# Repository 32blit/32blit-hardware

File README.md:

# 32Blit Hardware

This repository includes the schematic and STM32 Cube files for the 32Blit console.

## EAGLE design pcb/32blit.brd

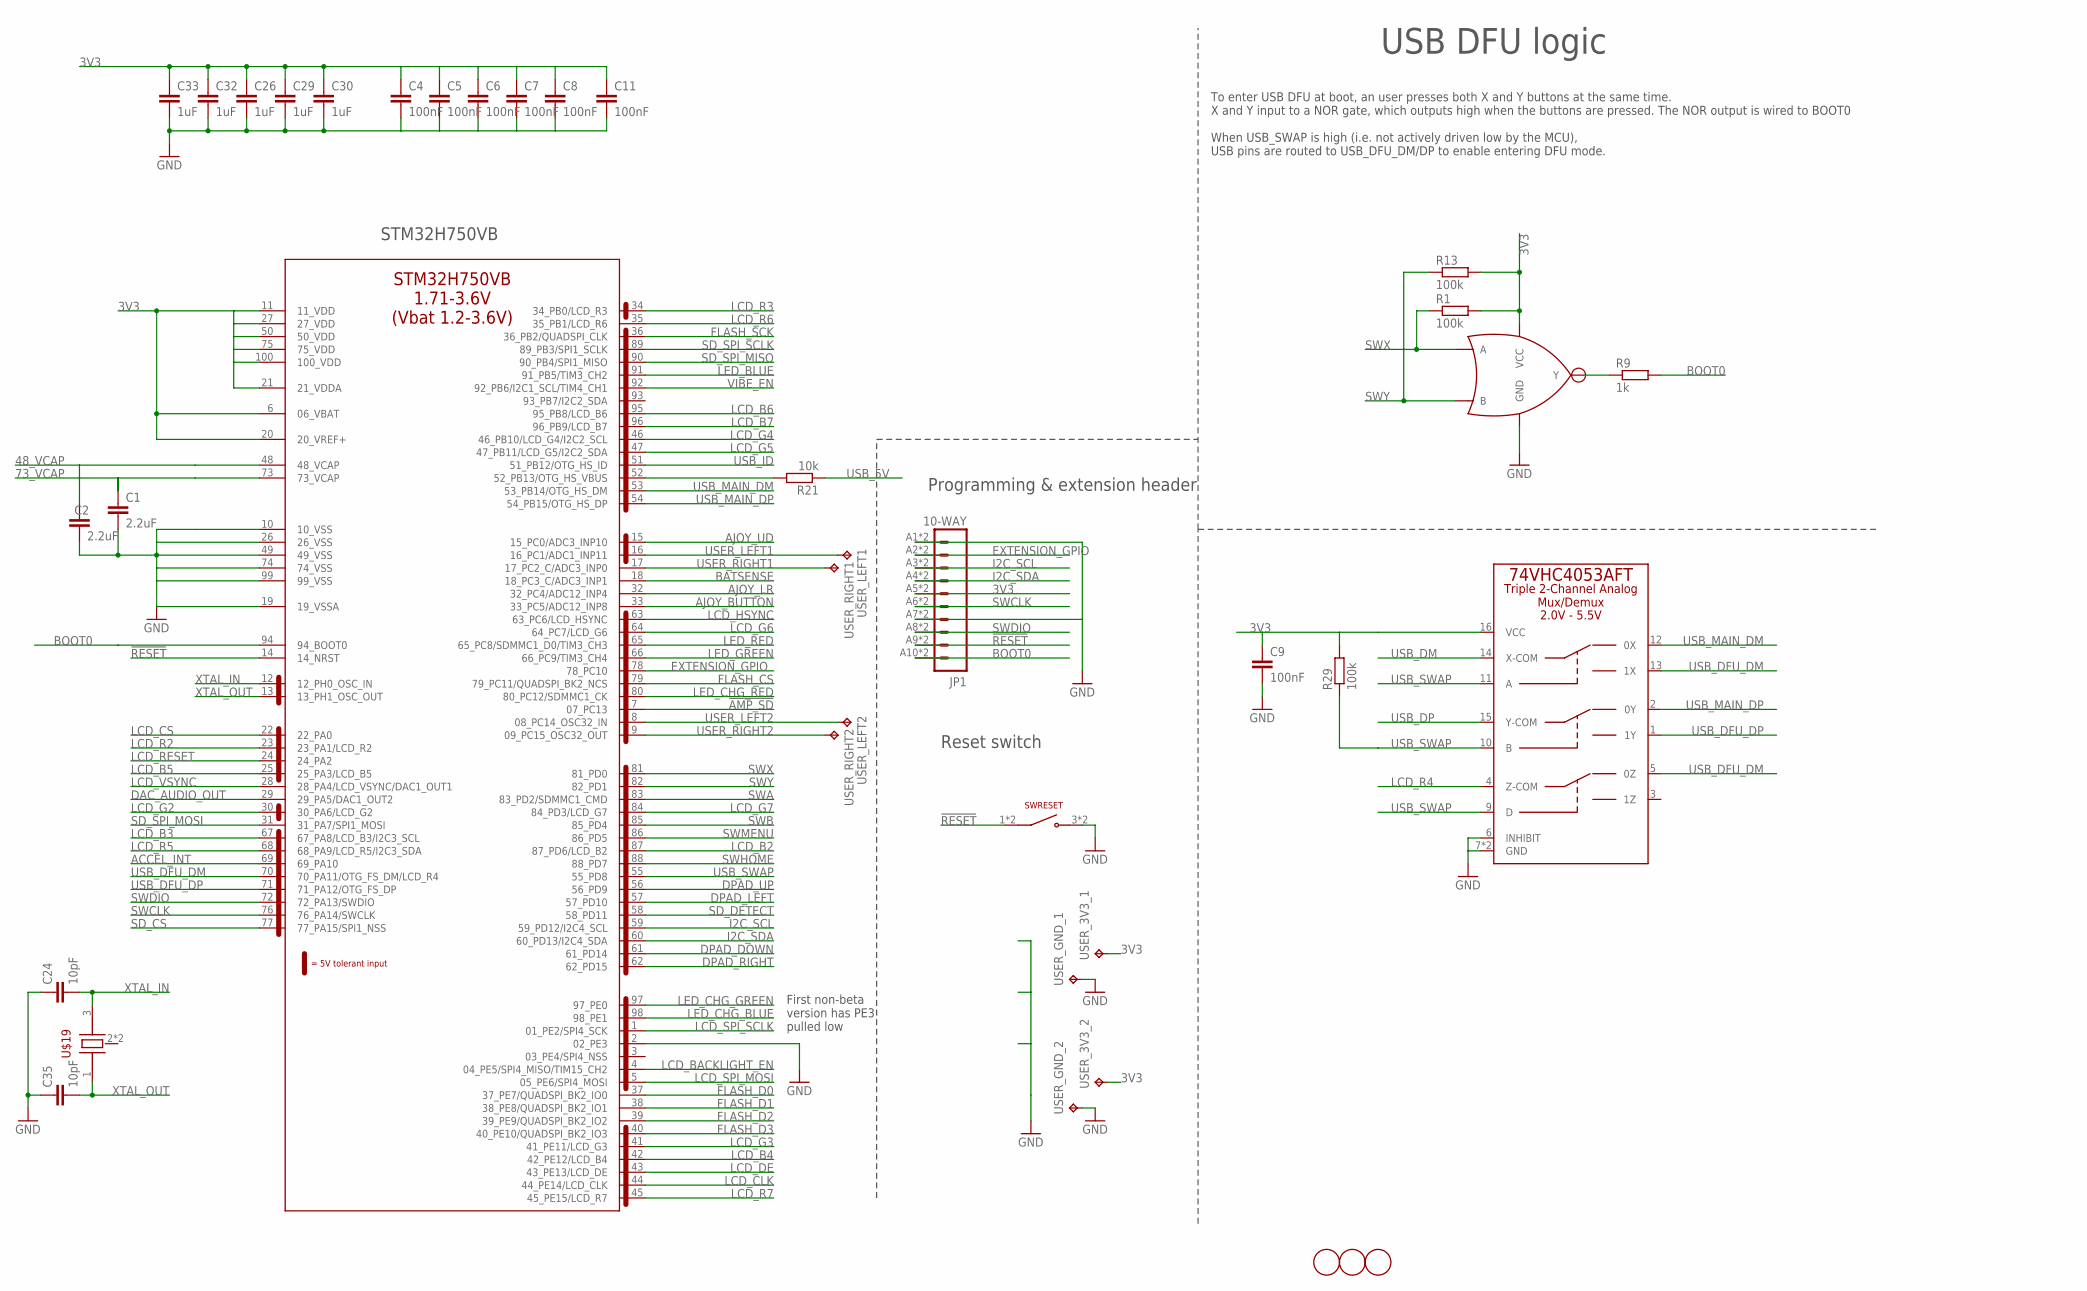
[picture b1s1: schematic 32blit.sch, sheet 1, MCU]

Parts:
C1, C2: 2.2uF; C0603
C4, C5, C6, C7, C8, C9, C11: 100nF; C0402K
C24, C35: 10pF; C0603K
C26, C29, C30, C32, C33: 1uF; C0603
JP1: 10-WAY; 1X10_FEMALE_SMT_RIGHT_ANGLE
R1, R13, R29: 100k; R0603
R9: 1k; R0603
R21: 10k; R0603
STM32H750: STM32H750VB; LQFP-100
SWRESET: LY-A03-02; TACT_RIGHT_ANGLE_LOW_PROFILE
U1: SN74AHC1G02; SOT-23-5
U8: 74VHC4053AFT; TSSOP-16-TI
U$17, U$22, U$23: FIDUCIAL1MM; FIDUCIAL-1MM
U$19: ABM8G-12.000MHZ-4Y-T3; TSX-3225
USER_3V3_1, USER_3V3_2: TPTP17SQ; TP17SQ
USER_GND_1, USER_GND_2: TPTP17SQ; TP17SQ
USER_LEFT1, USER_LEFT2: TPTP17SQ; TP17SQ
USER_RIGHT1, USER_RIGHT2: TPTP17SQ; TP17SQ

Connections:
3V3: C4.1, C5.1, C6.1, C7.1, C8.1, C9.1, C11.1, C26.1, C29.1, C30.1, C32.1, C33.1, JP1.A5 (5), JP1.B5 (5), R1.2, R13.2, R29.2, STM32H750.6 (06_VBAT), STM32H750.11 (11_VDD), STM32H750.20 (20_VREF+), STM32H750.21 (21_VDDA), STM32H750.27 (27_VDD), STM32H750.50 (50_VDD), STM32H750.75 (75_VDD), STM32H750.100 (100_VDD), U1.5 (VCC), U8.16 (VCC), USER_3V3_1.TP, USER_3V3_2.TP; also elsewhere on the board
48_VCAP: C2.1, STM32H750.48 (48_VCAP)
73_VCAP: C1.1, STM32H750.73 (73_VCAP)
!AMP_SD: STM32H750.7 (07_PC13); also elsewhere on the board
!RESET: JP1.A9 (9), JP1.B9 (9), STM32H750.14 (14_NRST), SWRESET.1, SWRESET.2 (1)
ACCEL_INT: STM32H750.69 (69_PA10); also elsewhere on the board
AJOY_BUTTON: STM32H750.33 (33_PC5/ADC12_INP8); also elsewhere on the board
AJOY_LR: STM32H750.32 (32_PC4/ADC12_INP4); also elsewhere on the board
AJOY_UD: STM32H750.15 (15_PC0/ADC3_INP10); also elsewhere on the board
BATSENSE: STM32H750.18 (18_PC3_C/ADC3_INP1); also elsewhere on the board
BOOT0: JP1.A10 (10), JP1.B10 (10), R9.2, STM32H750.94 (94_BOOT0)
DAC_AUDIO_OUT: STM32H750.29 (29_PA5/DAC1_OUT2); also elsewhere on the board
DPAD_DOWN: STM32H750.61 (61_PD14); also elsewhere on the board
DPAD_LEFT: STM32H750.57 (57_PD10); also elsewhere on the board
DPAD_RIGHT: STM32H750.62 (62_PD15); also elsewhere on the board
DPAD_UP: STM32H750.56 (56_PD9); also elsewhere on the board
EXTENSION_GPIO: JP1.A2 (2), JP1.B2 (2), STM32H750.78 (78_PC10)
FLASH_CS: STM32H750.79 (79_PC11/QUADSPI_BK2_NCS); also elsewhere on the board
FLASH_D0: STM32H750.37 (37_PE7/QUADSPI_BK2_IO0); also elsewhere on the board
FLASH_D1: STM32H750.38 (38_PE8/QUADSPI_BK2_IO1); also elsewhere on the board
FLASH_D2: STM32H750.39 (39_PE9/QUADSPI_BK2_IO2); also elsewhere on the board
FLASH_D3: STM32H750.40 (40_PE10/QUADSPI_BK2_IO3); also elsewhere on the board
FLASH_SCK: STM32H750.36 (36_PB2/QUADSPI_CLK); also elsewhere on the board
GND: C1.2, C2.2, C4.2, C5.2, C6.2, C7.2, C8.2, C9.2, C11.2, C24.1, C26.2, C29.2, C30.2, C32.2, C33.2, C35.1, JP1.A1 (1), JP1.A7 (7), JP1.B1 (1), JP1.B7 (7), STM32H750.2 (02_PE3), STM32H750.10 (10_VSS), STM32H750.19 (19_VSSA), STM32H750.26 (26_VSS), STM32H750.49 (49_VSS), STM32H750.74 (74_VSS), STM32H750.99 (99_VSS), SWRESET.3 (2), SWRESET.4 (2), U1.3 (GND), U8.6 (INHIBIT), U8.7 (GND), U8.8 (GND), USER_GND_1.TP, USER_GND_2.TP; also elsewhere on the board
I2C_SCL: JP1.A3 (3), JP1.B3 (3), STM32H750.59 (59_PD12/I2C4_SCL); also elsewhere on the board
I2C_SDA: JP1.A4 (4), JP1.B4 (4), STM32H750.60 (60_PD13/I2C4_SDA); also elsewhere on the board
LCD_B2: STM32H750.87 (87_PD6/LCD_B2); also elsewhere on the board
LCD_B3: STM32H750.67 (67_PA8/LCD_B3/I2C3_SCL); also elsewhere on the board
LCD_B4: STM32H750.42 (42_PE12/LCD_B4); also elsewhere on the board
LCD_B5: STM32H750.25 (25_PA3/LCD_B5); also elsewhere on the board
LCD_B6: STM32H750.95 (95_PB8/LCD_B6); also elsewhere on the board
LCD_B7: STM32H750.96 (96_PB9/LCD_B7); also elsewhere on the board
LCD_BACKLIGHT_EN: STM32H750.4 (04_PE5/SPI4_MISO/TIM15_CH2); also elsewhere on the board
LCD_CLK: STM32H750.44 (44_PE14/LCD_CLK); also elsewhere on the board
LCD_CS: STM32H750.22 (22_PA0); also elsewhere on the board
LCD_DE: STM32H750.43 (43_PE13/LCD_DE); also elsewhere on the board
LCD_G2: STM32H750.30 (30_PA6/LCD_G2); also elsewhere on the board
LCD_G3: STM32H750.41 (41_PE11/LCD_G3); also elsewhere on the board
LCD_G4: STM32H750.46 (46_PB10/LCD_G4/I2C2_SCL); also elsewhere on the board
LCD_G5: STM32H750.47 (47_PB11/LCD_G5/I2C2_SDA); also elsewhere on the board
LCD_G6: STM32H750.64 (64_PC7/LCD_G6); also elsewhere on the board
LCD_G7: STM32H750.84 (84_PD3/LCD_G7); also elsewhere on the board
LCD_HSYNC: STM32H750.63 (63_PC6/LCD_HSYNC); also elsewhere on the board
LCD_R2: STM32H750.23 (23_PA1/LCD_R2); also elsewhere on the board
LCD_R3: STM32H750.34 (34_PB0/LCD_R3); also elsewhere on the board
LCD_R4: U8.4 (Z-COM); also elsewhere on the board
LCD_R5: STM32H750.68 (68_PA9/LCD_R5/I2C3_SDA); also elsewhere on the board
LCD_R6: STM32H750.35 (35_PB1/LCD_R6); also elsewhere on the board
LCD_R7: STM32H750.45 (45_PE15/LCD_R7); also elsewhere on the board
LCD_RESET: STM32H750.24 (24_PA2); also elsewhere on the board
LCD_SPI_MOSI: STM32H750.5 (05_PE6/SPI4_MOSI); also elsewhere on the board
LCD_SPI_SCLK: STM32H750.1 (01_PE2/SPI4_SCK); also elsewhere on the board
LCD_VSYNC: STM32H750.28 (28_PA4/LCD_VSYNC/DAC1_OUT1); also elsewhere on the board
LED_BLUE: STM32H750.91 (91_PB5/TIM3_CH2); also elsewhere on the board
LED_CHG_BLUE: STM32H750.98 (98_PE1); also elsewhere on the board
LED_CHG_GREEN: STM32H750.97 (97_PE0); also elsewhere on the board
LED_CHG_RED: STM32H750.80 (80_PC12/SDMMC1_CK); also elsewhere on the board
LED_GREEN: STM32H750.66 (66_PC9/TIM3_CH4); also elsewhere on the board
LED_RED: STM32H750.65 (65_PC8/SDMMC1_D0/TIM3_CH3); also elsewhere on the board
unnamed: R9.1, U1.4 (Y)
unnamed: R21.2, STM32H750.52 (52_PB13/OTG_HS_VBUS)
SD_CS: STM32H750.77 (77_PA15/SPI1_NSS); also elsewhere on the board
SD_DETECT: STM32H750.58 (58_PD11); also elsewhere on the board
SD_SPI_MISO: STM32H750.90 (90_PB4/SPI1_MISO); also elsewhere on the board
SD_SPI_MOSI: STM32H750.31 (31_PA7/SPI1_MOSI); also elsewhere on the board
SD_SPI_SCLK: STM32H750.89 (89_PB3/SPI1_SCLK); also elsewhere on the board
SWA: STM32H750.83 (83_PD2/SDMMC1_CMD); also elsewhere on the board
SWB: STM32H750.85 (85_PD4); also elsewhere on the board
SWCLK: JP1.A6 (6), JP1.B6 (6), STM32H750.76 (76_PA14/SWCLK)
SWDIO: JP1.A8 (8), JP1.B8 (8), STM32H750.72 (72_PA13/SWDIO)
SWHOME: STM32H750.88 (88_PD7); also elsewhere on the board
SWMENU: STM32H750.86 (86_PD5); also elsewhere on the board
SWX: R1.1, STM32H750.81 (81_PD0), U1.1 (A); also elsewhere on the board
SWY: R13.1, STM32H750.82 (82_PD1), U1.2 (B); also elsewhere on the board
USB_5V: R21.1; also elsewhere on the board
USB_DFU_DM: STM32H750.70 (70_PA11/OTG_FS_DM/LCD_R4), U8.5 (0Z), U8.13 (1X)
USB_DFU_DP: STM32H750.71 (71_PA12/OTG_FS_DP), U8.1 (1Y)
USB_DM: U8.14 (X-COM); also elsewhere on the board
USB_DP: U8.15 (Y-COM); also elsewhere on the board
USB_ID: STM32H750.51 (51_PB12/OTG_HS_ID); also elsewhere on the board
USB_MAIN_DM: STM32H750.53 (53_PB14/OTG_HS_DM), U8.12 (0X)
USB_MAIN_DP: STM32H750.54 (54_PB15/OTG_HS_DP), U8.2 (0Y)
USB_SWAP: R29.1, STM32H750.55 (55_PD8), U8.9 (D), U8.10 (B), U8.11 (A)
USER_LEFT1: STM32H750.16 (16_PC1/ADC1_INP11), USER_LEFT1.TP
USER_LEFT2: STM32H750.8 (08_PC14_OSC32_IN), USER_LEFT2.TP
USER_RIGHT1: STM32H750.17 (17_PC2_C/ADC3_INP0), USER_RIGHT1.TP
USER_RIGHT2: STM32H750.9 (09_PC15_OSC32_OUT), USER_RIGHT2.TP
VIBE_EN: STM32H750.92 (92_PB6/I2C1_SCL/TIM4_CH1); also elsewhere on the board
XTAL_IN: C24.2, STM32H750.12 (12_PH0_OSC_IN), U$19.3 (2)
XTAL_OUT: C35.2, STM32H750.13 (13_PH1_OSC_OUT), U$19.1

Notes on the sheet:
STM32H750VB
Programming & extension header
Reset switch
To enter USB DFU at boot, an user presses both X and Y buttons at the same time. X and Y input to a NOR gate, which outputs high when the buttons are pressed. The NOR output is wired to BOOT0 When USB_SWAP is high (i.e. not actively driven low by the MCU), USB pins are routed to USB_DFU_DM/DP to en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
USB DFU logic
First non-beta version has PE3 pulled low

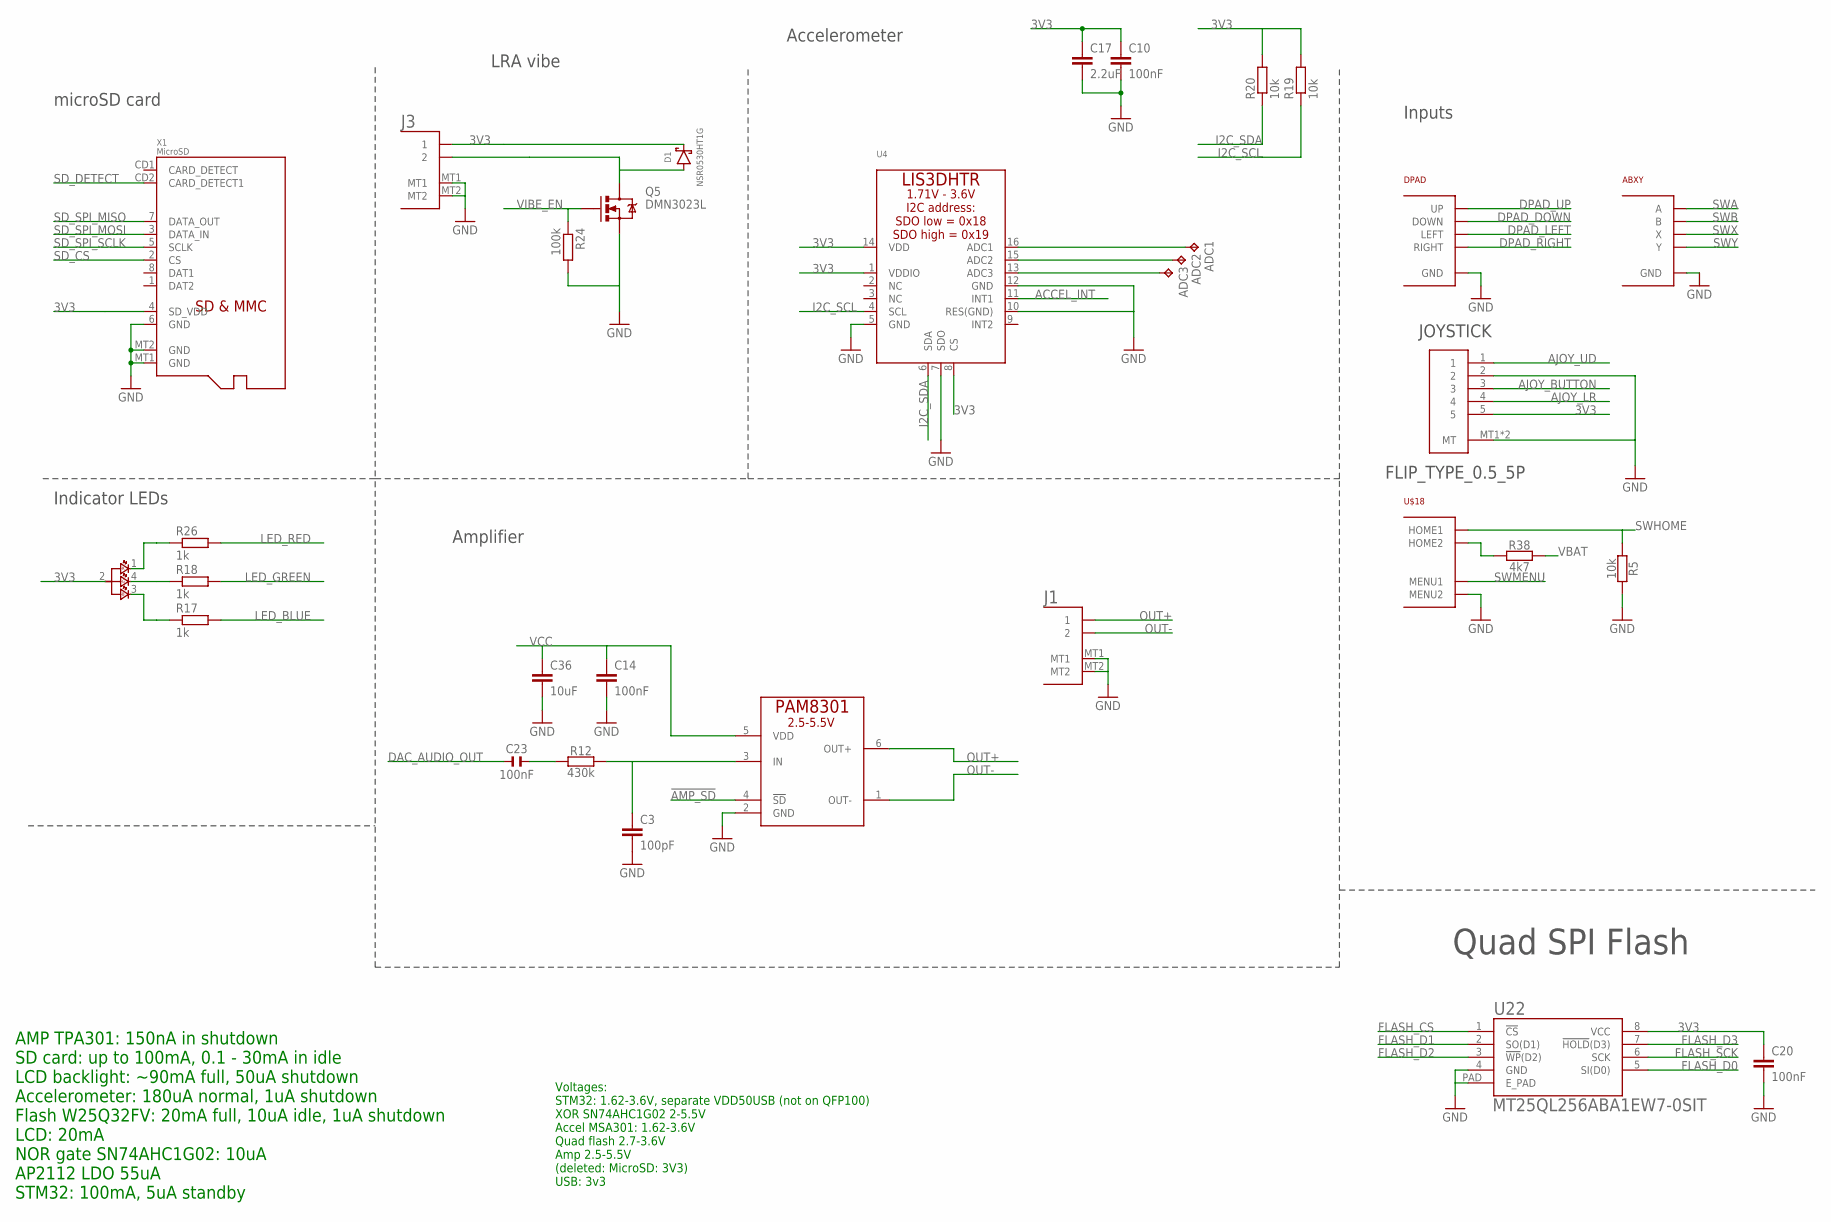
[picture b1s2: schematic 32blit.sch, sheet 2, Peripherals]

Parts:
ABXY: ABXY
ADC1, ADC2, ADC3: TPTP17SQ; TP17SQ
C3: 100pF; C0603
C10, C14, C20: 100nF; C0402K
C17: 2.2uF; C0603
C23: 100nF; 0402
C36: 10uF; C0805
D1: NSR0530HT1G; SOD-323
DPAD: DPAD
J1: 1X02PICOBLADE; PICOBLADE_1.25MM_2P
J3: 1X02JST_SH; JST_SH_1.0MM_2P
JOYSTICK: FLIP_TYPE_0.5_5P; FPC-0.5MM-05WAY
Q5: DMN3023L; SOT23
R5, R19, R20: 10k; R0603
R12: 430k; R0603
R17, R18, R26: 1k; R0603
R24: 100k; R0603
R38: 4k7; R0603
RGB2: LED_RGB_4P6028_REVERSE; LED-6028_REVERSE_RGB
U4: ACCEL_LIS3DHTR; LGA16_3X3MM
U5: PAM8301; SOT-23-6
U22: MT25QL256ABA1EW7-0SIT; DFN-8_6X5MM
U$18: HOME-MENU; MENU-HOME
X1: MicroSD; MICROSD

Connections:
3V3: C10.1, C17.1, C20.1, D1.C, J3.1, JOYSTICK.5, R19.2, R20.2, RGB2.2 (A), U4.1 (VDDIO), U4.8 (CS), U4.14 (VDD), U22.8 (VCC), X1.4 (SD_VDD); also elsewhere on the board
!AMP_SD: U5.4 (!SD); also elsewhere on the board
ACCEL_INT: U4.11 (INT1); also elsewhere on the board
AJOY_BUTTON: JOYSTICK.3; also elsewhere on the board
AJOY_LR: JOYSTICK.4; also elsewhere on the board
AJOY_UD: JOYSTICK.1; also elsewhere on the board
DAC_AUDIO_OUT: C23.2; also elsewhere on the board
DPAD_DOWN: DPAD.DOWN; also elsewhere on the board
DPAD_LEFT: DPAD.LEFT; also elsewhere on the board
DPAD_RIGHT: DPAD.RIGHT; also elsewhere on the board
DPAD_UP: DPAD.UP; also elsewhere on the board
FLASH_CS: U22.1 (!CS); also elsewhere on the board
FLASH_D0: U22.5 (SI(D0)); also elsewhere on the board
FLASH_D1: U22.2 (SO(D1)); also elsewhere on the board
FLASH_D2: U22.3 (!WP!(D2)); also elsewhere on the board
FLASH_D3: U22.7 (!HOLD!(D3)); also elsewhere on the board
FLASH_SCK: U22.6 (SCK); also elsewhere on the board
GND: ABXY.GND1 (GND), ABXY.GND2 (GND), ABXY.GND3 (GND), ABXY.GND4 (GND), C3.2, C10.2, C14.2, C17.2, C20.2, C36.2, DPAD.GND1 (GND), DPAD.GND2 (GND), DPAD.GND3 (GND), DPAD.GND4 (GND), J1.MT1, J1.MT2, J3.MT1, J3.MT2, JOYSTICK.2, JOYSTICK.MT1 (MT), JOYSTICK.MT2 (MT), Q5.2 (S), R5.2, R24.2, U4.5 (GND), U4.7 (SDO), U4.10 (RES(GND)), U4.12 (GND), U5.2 (GND), U22.4 (GND), U22.PAD (E_PAD), U$18.GND3 (MENU2), X1.6 (GND), X1.MT1 (GND), X1.MT2 (GND); also elsewhere on the board
I2C_SCL: R19.1, U4.4 (SCL); also elsewhere on the board
I2C_SDA: R20.1, U4.6 (SDA); also elsewhere on the board
LED_BLUE: R17.2; also elsewhere on the board
LED_GREEN: R18.2; also elsewhere on the board
LED_RED: R26.2; also elsewhere on the board
unnamed: ADC3.TP, U4.13 (ADC3)
unnamed: C3.1, R12.2, U5.3 (IN)
unnamed: R18.1, RGB2.4 (GC)
unnamed: R17.1, RGB2.3 (BC)
unnamed: C23.1, R12.1
unnamed: ADC2.TP, U4.15 (ADC2)
unnamed: ADC1.TP, U4.16 (ADC1)
unnamed: D1.A, J3.2, Q5.3 (D)
unnamed: R26.1, RGB2.1 (RC)
unnamed: R38.1, U$18.GND4 (HOME2)
OUT+: J1.1, U5.6 (OUT+)
OUT-: J1.2, U5.1 (OUT-)
SD_CS: X1.2 (CS); also elsewhere on the board
SD_DETECT: X1.CD2 (CARD_DETECT1); also elsewhere on the board
SD_SPI_MISO: X1.7 (DATA_OUT); also elsewhere on the board
SD_SPI_MOSI: X1.3 (DATA_IN); also elsewhere on the board
SD_SPI_SCLK: X1.5 (SCLK); also elsewhere on the board
SWA: ABXY.A; also elsewhere on the board
SWB: ABXY.B; also elsewhere on the board
SWHOME: R5.1, U$18.HOME (HOME1); also elsewhere on the board
SWMENU: U$18.MENU (MENU1); also elsewhere on the board
SWX: ABXY.X; also elsewhere on the board
SWY: ABXY.Y; also elsewhere on the board
VBAT: R38.2; also elsewhere on the board
VCC: C14.1, C36.1, U5.5 (VDD); also elsewhere on the board
VIBE_EN: Q5.1 (G), R24.1; also elsewhere on the board

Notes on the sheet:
Quad SPI Flash
Accelerometer
Inputs
Indicator LEDs
Amplifier
AMP TPA301: 150nA in shutdown SD card: up to 100mA, 0.1 - 30mA in idle LCD backlight: ~90mA full, 50uA shutdown Accelerometer: 180uA normal, 1uA shutdown Flash W25Q32FV: 20mA full, 10uA idle, 1uA shutdown LCD: 20mA NOR gate SN74AHC1G02: 10uA AP2112 LDO 55uA STM32: 100mA, 5uA standby
Voltages: STM32: 1.62-3.6V, separate VDD50USB (not on QFP100) XOR SN74AHC1G02 2-5.5V Accel MSA301: 1.62-3.6V Quad flash 2.7-3.6V Amp 2.5-5.5V (deleted: MicroSD: 3V3) USB: 3v3
LRA vibe
microSD card

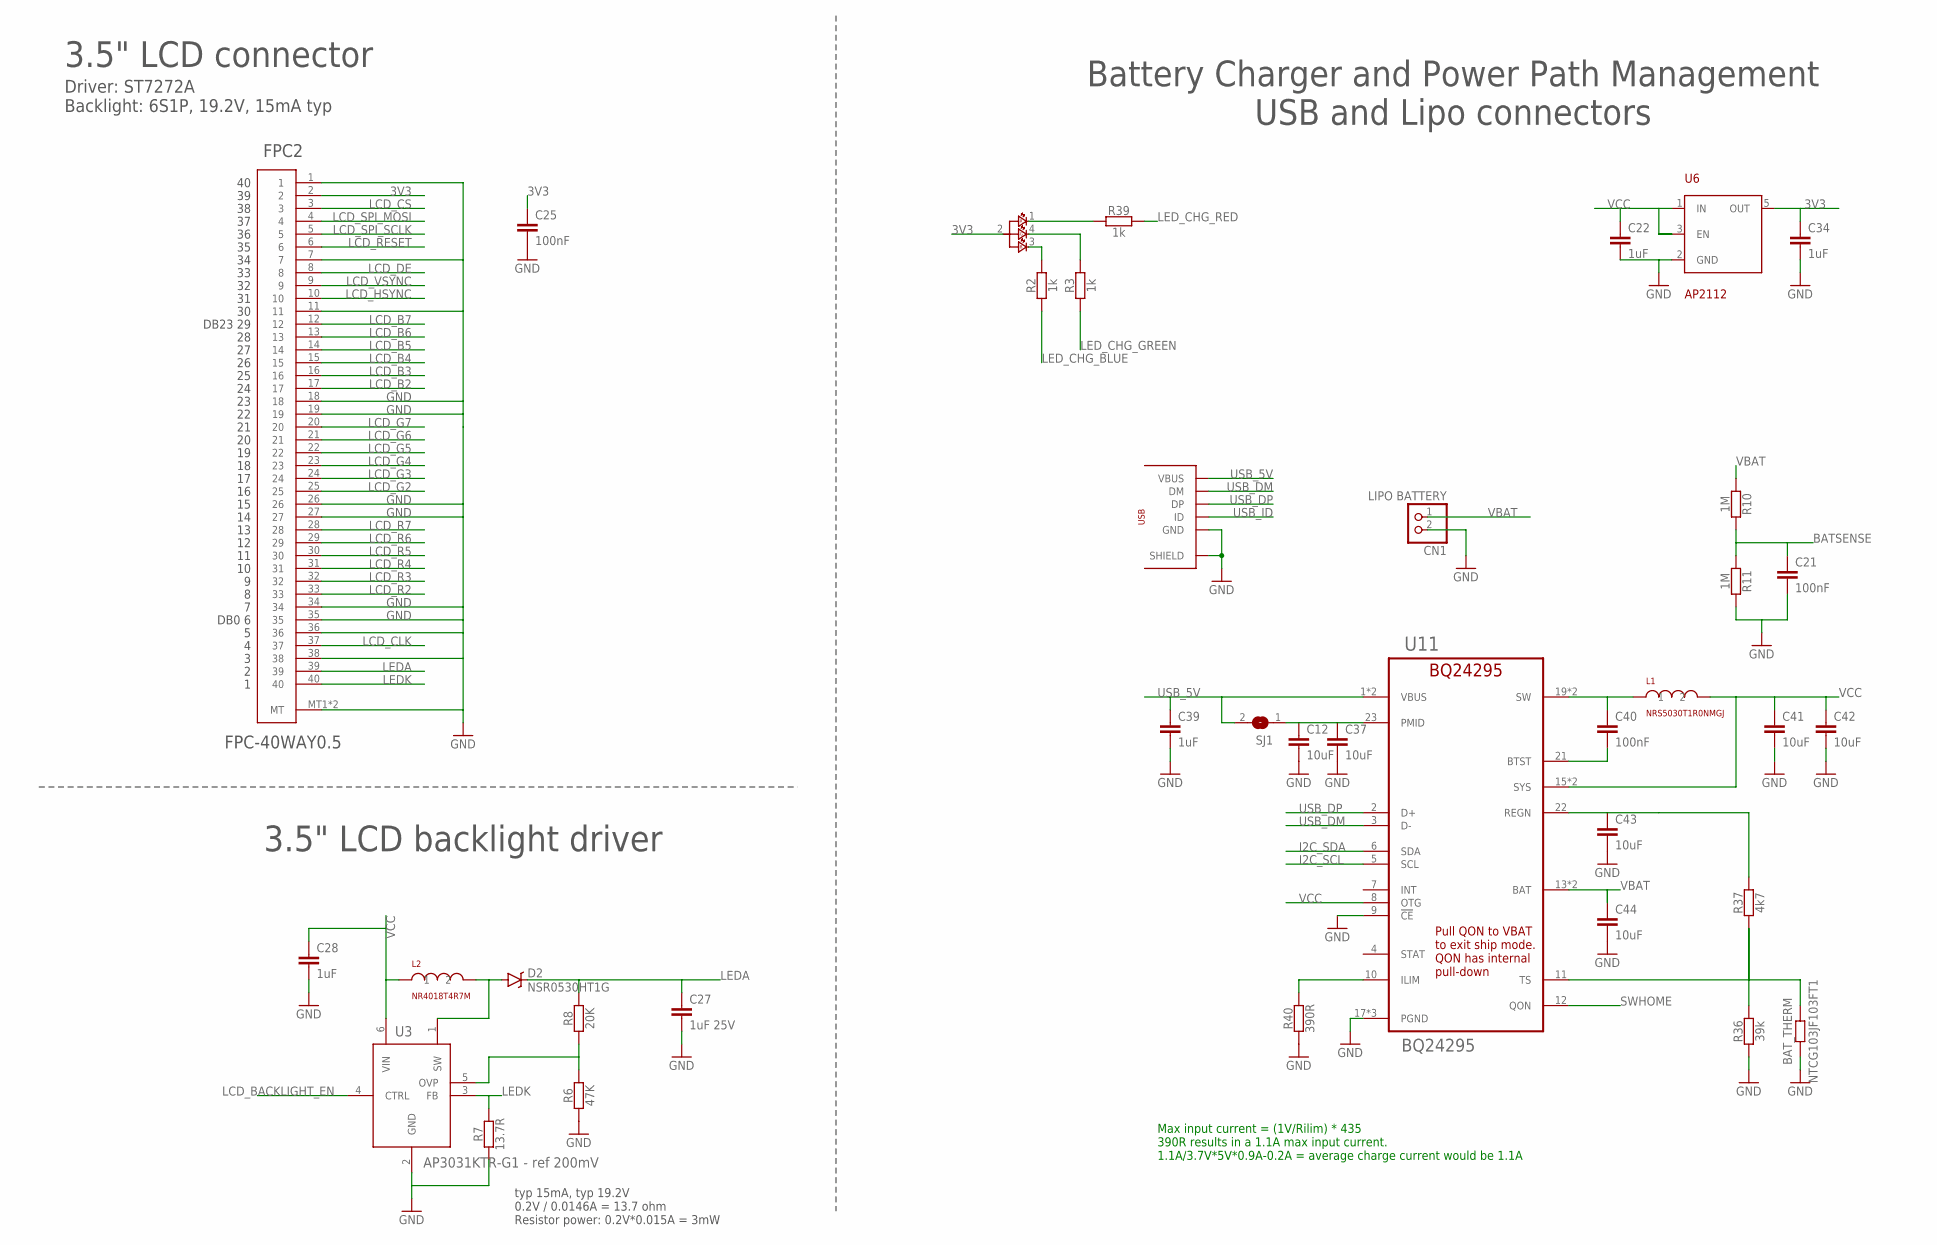
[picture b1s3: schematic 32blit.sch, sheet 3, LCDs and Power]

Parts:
BAT_THERM: NTCG103JF103FT1; 0402@1
C12, C37, C41, C42, C43, C44: 10uF; C0805
C21, C25, C40: 100nF; C0402K
C22, C28, C34, C39: 1uF; C0603
C27: 1uF 25V; C0603
CN1: LIPO BATTERY; JST-PH-2-SMT-RA
D2: NSR0530HT1G
FPC2: FPC-40WAY0.5; FPC-0.5MM-40WAY
L1: NRS5030T1R0NMGJ; NRS5030
L2: NR4018T4R7M; NR4018
R2, R3, R39: 1k; R0603
R6: 47K; R0603
R7: 13.7R; R0603
R8: 20K; R0603
R10, R11: 1M; R0603
R36: 39k; R0603
R37: 4k7; R0603
R40: 390R; R0603
RGB1: LED_RGB_4P6028_REVERSE; LED-6028_REVERSE_RGB
SJ1: SOLDERJUMPER; SOLDERJUMPER_ARROW_NOPASTE
U3: AP3031KTR-G1 - ref 200mV; SOT23-6L
U6: AP2112; SOT-23-5
U11: BQ24295; QFN50P400X400X100-25N
U$3: FCI 10118193-0001LF; MICROB-USB

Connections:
3V3: C25.1, C34.1, FPC2.2, RGB1.2 (A), U6.5 (OUT); also elsewhere on the board
BATSENSE: C21.1, R10.2, R11.1; also elsewhere on the board
GND: BAT_THERM.1, C12.2, C21.2, C22.2, C25.2, C27.2, C28.2, C34.2, C37.2, C39.2, C41.2, C42.2, C43.2, C44.2, CN1.2 (1), FPC2.1, FPC2.7, FPC2.11, FPC2.18, FPC2.19, FPC2.26, FPC2.27, FPC2.34, FPC2.35, FPC2.36, FPC2.38, FPC2.MT1 (MT), FPC2.MT2 (MT), R6.1, R7.1, R11.2, R36.1, R40.1, U3.2 (GND), U6.2 (GND), U11.9 (!CE), U11.17 (PGND), U11.18 (PGND), U11.25 (PGND), U$3.GND, U$3.SH1 (SHIELD), U$3.SH2 (SHIELD), U$3.SH3 (SHIELD), U$3.SH4 (SHIELD), U$3.SH5 (SHIELD), U$3.SH6 (SHIELD), U$3.SH7 (SHIELD), U$3.SH8 (SHIELD); also elsewhere on the board
I2C_SCL: U11.5 (SCL); also elsewhere on the board
I2C_SDA: U11.6 (SDA); also elsewhere on the board
LCD_B2: FPC2.17; also elsewhere on the board
LCD_B3: FPC2.16; also elsewhere on the board
LCD_B4: FPC2.15; also elsewhere on the board
LCD_B5: FPC2.14; also elsewhere on the board
LCD_B6: FPC2.13; also elsewhere on the board
LCD_B7: FPC2.12; also elsewhere on the board
LCD_BACKLIGHT_EN: U3.4 (CTRL); also elsewhere on the board
LCD_CLK: FPC2.37; also elsewhere on the board
LCD_CS: FPC2.3; also elsewhere on the board
LCD_DE: FPC2.8; also elsewhere on the board
LCD_G2: FPC2.25; also elsewhere on the board
LCD_G3: FPC2.24; also elsewhere on the board
LCD_G4: FPC2.23; also elsewhere on the board
LCD_G5: FPC2.22; also elsewhere on the board
LCD_G6: FPC2.21; also elsewhere on the board
LCD_G7: FPC2.20; also elsewhere on the board
LCD_HSYNC: FPC2.10; also elsewhere on the board
LCD_R2: FPC2.33; also elsewhere on the board
LCD_R3: FPC2.32; also elsewhere on the board
LCD_R4: FPC2.31; also elsewhere on the board
LCD_R5: FPC2.30; also elsewhere on the board
LCD_R6: FPC2.29; also elsewhere on the board
LCD_R7: FPC2.28; also elsewhere on the board
LCD_RESET: FPC2.6; also elsewhere on the board
LCD_SPI_MOSI: FPC2.4; also elsewhere on the board
LCD_SPI_SCLK: FPC2.5; also elsewhere on the board
LCD_VSYNC: FPC2.9; also elsewhere on the board
LEDA: C27.1, D2.C, FPC2.39, R8.2
LEDK: FPC2.40, R7.2, U3.3 (FB)
LED_CHG_BLUE: R2.1; also elsewhere on the board
LED_CHG_GREEN: R3.1; also elsewhere on the board
LED_CHG_RED: R39.2; also elsewhere on the board
unnamed: D2.A, L2.2, U3.1 (SW)
unnamed: R2.2, RGB1.3 (BC)
unnamed: R3.2, RGB1.4 (GC)
unnamed: R39.1, RGB1.1 (RC)
unnamed: R6.2, R8.1, U3.5 (OVP)
unnamed: R40.2, U11.10 (ILIM)
unnamed: C40.2, U11.21 (BTST)
unnamed: BAT_THERM.2, R36.2, R37.1, U11.11 (TS)
unnamed: C40.1, L1.1, U11.19 (SW), U11.20 (SW)
unnamed: C12.1, C37.1, SJ1.1, U11.23 (PMID)
REGN: C43.1, R37.2, U11.22 (REGN)
SWHOME: U11.12 (QON); also elsewhere on the board
USB_5V: C39.1, SJ1.2, U11.1 (VBUS), U11.24 (VBUS), U$3.VBUS; also elsewhere on the board
USB_DM: U11.3 (D-), U$3.DM; also elsewhere on the board
USB_DP: U11.2 (D+), U$3.DP; also elsewhere on the board
USB_ID: U$3.ID; also elsewhere on the board
VBAT: C44.1, CN1.1 (2), R10.1, U11.13 (BAT), U11.14 (BAT); also elsewhere on the board
VCC: C22.1, C28.1, C41.1, C42.1, L1.2, L2.1, U3.6 (VIN), U6.1 (IN), U6.3 (EN), U11.8 (OTG), U11.15 (SYS), U11.16 (SYS); also elsewhere on the board

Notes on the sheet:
3.5" LCD connector
Driver: ST7272A Backlight: 6S1P, 19.2V, 15mA typ
typ 15mA, typ 19.2V 0.2V / 0.0146A = 13.7 ohm Resistor power: 0.2V*0.015A = 3mW
3.5" LCD backlight driver
Battery Charger and Power Path Management USB and Lipo connectors
Max input current = (1V/Rilim) * 435 390R results in a 1.1A max input current. 1.1A/3.7V*5V*0.9A-0.2A = average charge current would be 1.1A
DB0 6
DB23 29

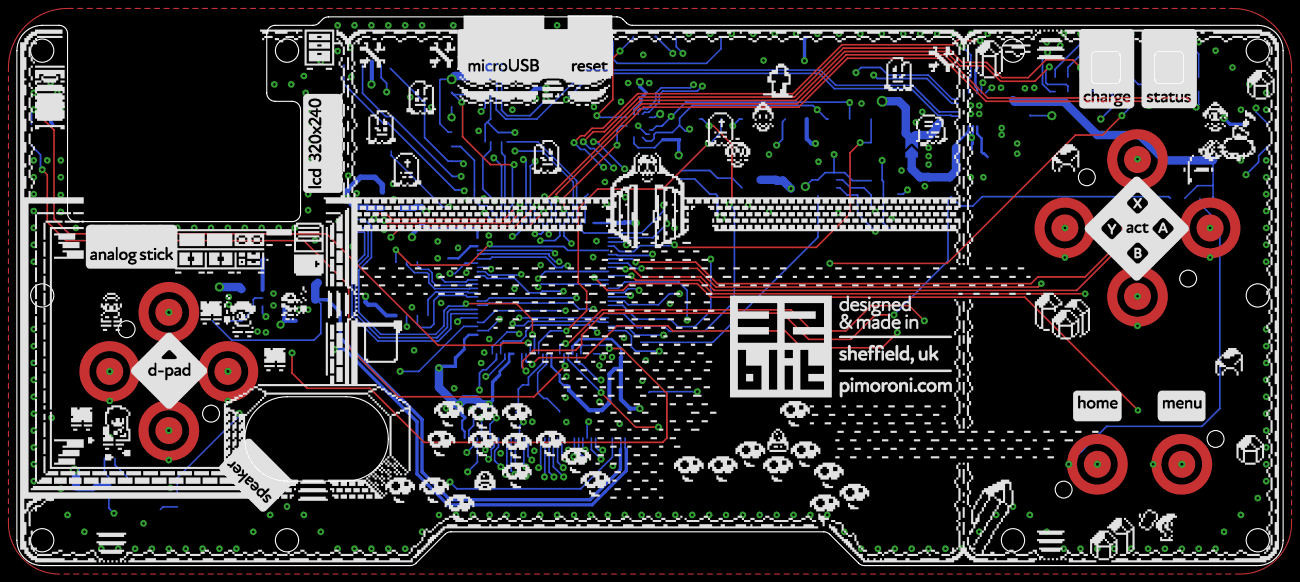
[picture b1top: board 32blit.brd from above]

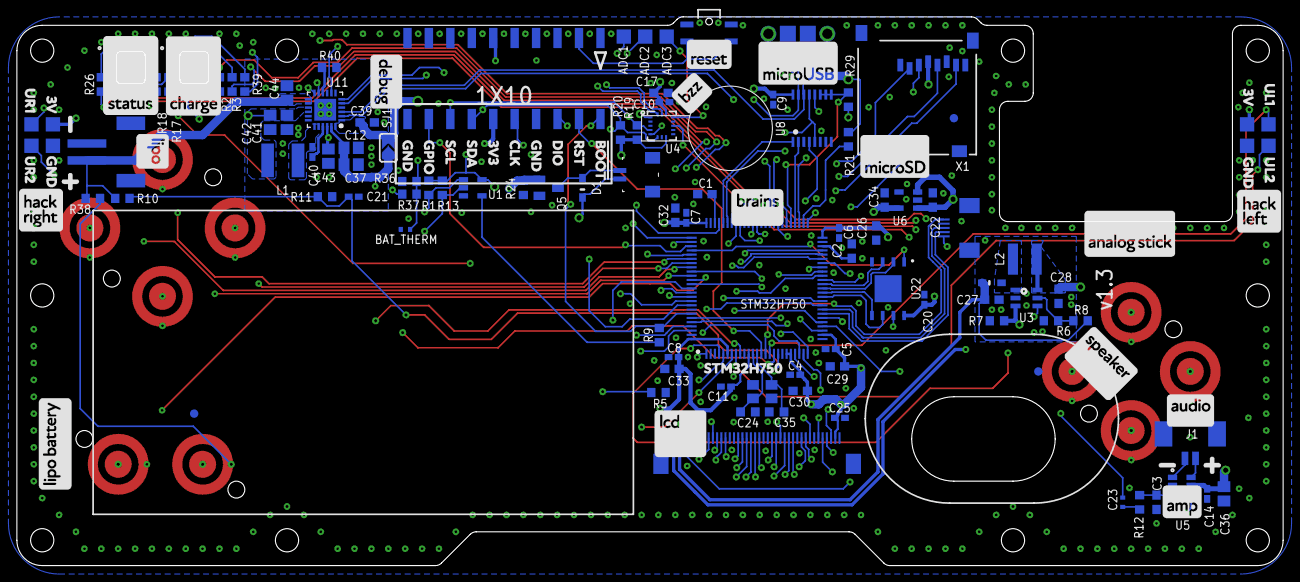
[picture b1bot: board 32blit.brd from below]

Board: 4 copper layers, 150.0 x 65.0 mm, 121 parts (106 on the bottom side), 117 nets.

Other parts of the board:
U$2: LRA_ELV1030AC1
U$6, U$8, U$9, U$10, U$11, U$12, U$13, U$14, U$16, U$20: 2.7MM-MOUNTING-HOLE
U$7: LCD_035
U$15: 3020_SPEAKER
U$21: JOYSTICK_ANALOG

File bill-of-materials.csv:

"Part";"Value";"Device";"Package";"Description";"";
"ABXY";"ABXY";"ABXY";"ABXY";"";"";
"ADC1";"TPTP17SQ";"TPTP17SQ";"TP17SQ";"Test pad";"";
"ADC2";"TPTP17SQ";"TPTP17SQ";"TP17SQ";"Test pad";"";
"ADC3";"TPTP17SQ";"TPTP17SQ";"TP17SQ";"Test pad";"";
"BAT_THERM";"NTCG103JF103FT1";"RESISTOR.0402";"0402@1";"";"";
"C1";"2.2uF";"C-EUC0603";"C0603";"CAPACITOR, European symbol";"";
"C2";"2.2uF";"C-EUC0603";"C0603";"CAPACITOR, European symbol";"";
"C3";"100pF";"C-EUC0603";"C0603";"CAPACITOR, European symbol";"";
"C4";"100nF";"C-EUC0402K";"C0402K";"CAPACITOR, European symbol";"";
"C5";"100nF";"C-EUC0402K";"C0402K";"CAPACITOR, European symbol";"";
"C6";"100nF";"C-EUC0402K";"C0402K";"CAPACITOR, European symbol";"";
"C7";"100nF";"C-EUC0402K";"C0402K";"CAPACITOR, European symbol";"";
"C8";"100nF";"C-EUC0402K";"C0402K";"CAPACITOR, European symbol";"";
"C9";"100nF";"C-EUC0402K";"C0402K";"CAPACITOR, European symbol";"";
"C10";"100nF";"C-EUC0402K";"C0402K";"CAPACITOR, European symbol";"";
"C11";"100nF";"C-EUC0402K";"C0402K";"CAPACITOR, European symbol";"";
"C12";"10uF";"C-EUC0805";"C0805";"CAPACITOR, European symbol";"";
"C14";"100nF";"C-EUC0402K";"C0402K";"CAPACITOR, European symbol";"";
"C17";"2.2uF";"C-EUC0603";"C0603";"CAPACITOR, European symbol";"";
"C20";"100nF";"C-EUC0402K";"C0402K";"CAPACITOR, European symbol";"";
"C21";"100nF";"C-EUC0402K";"C0402K";"CAPACITOR, European symbol";"";
"C22";"1uF";"C-EUC0603";"C0603";"CAPACITOR, European symbol";"";
"C23";"100nF";"CAPACITOR.0402";"0402";"";"";
"C24";"10pF";"C-EUC0603K";"C0603K";"CAPACITOR, European symbol";"";
"C25";"100nF";"C-EUC0402K";"C0402K";"CAPACITOR, European symbol";"";
"C26";"1uF";"C-EUC0603";"C0603";"CAPACITOR, European symbol";"";
"C27";"1uF 25V";"C-EUC0603";"C0603";"CAPACITOR, European symbol";"";
"C28";"1uF";"C-EUC0603";"C0603";"CAPACITOR, European symbol";"";
"C29";"1uF";"C-EUC0603";"C0603";"CAPACITOR, European symbol";"";
"C30";"1uF";"C-EUC0603";"C0603";"CAPACITOR, European symbol";"";
"C32";"1uF";"C-EUC0603";"C0603";"CAPACITOR, European symbol";"";
"C33";"1uF";"C-EUC0603";"C0603";"CAPACITOR, European symbol";"";
"C34";"1uF";"C-EUC0603";"C0603";"CAPACITOR, European symbol";"";
"C35";"10pF";"C-EUC0603K";"C0603K";"CAPACITOR, European symbol";"";
"C36";"10uF";"C-EUC0805";"C0805";"CAPACITOR, European symbol";"";
"C37";"10uF";"C-EUC0805";"C0805";"CAPACITOR, European symbol";"";
"C39";"1uF";"C-EUC0603";"C0603";"CAPACITOR, European symbol";"";
"C40";"100nF";"C-EUC0402K";"C0402K";"CAPACITOR, European symbol";"";
"C41";"10uF";"C-EUC0805";"C0805";"CAPACITOR, European symbol";"";
"C42";"10uF";"C-EUC0805";"C0805";"CAPACITOR, European symbol";"";
"C43";"10uF";"C-EUC0805";"C0805";"CAPACITOR, European symbol";"";
"C44";"10uF";"C-EUC0805";"C0805";"CAPACITOR, European symbol";"";
"CN1";"LIPO BATTERY";"JST_2PIN-SMT-RA";"JST-PH-2-SMT-RA";"JST 2-Pin Connectors of various flavors";"";
"D1";"NSR0530HT1G";"DIODE-SCHOTTKY";"SOD-323";"";"";
"D2";"NSR0530HT1G";"NSR0530HT1G";"NSR0530HT1G";"";"";
"DPAD";"DPAD";"DPAD";"DPAD";"";"";
"FPC2";"FPC-40WAY0.5";"FPC-40WAY0.5";"FPC-0.5MM-40WAY";"";"";
"J1";"1X02PICOBLADE";"1X02PICOBLADE";"PICOBLADE_1.25MM_2P";"";"";
"J3";"1X02JST_SH";"1X02JST_SH";"JST_SH_1.0MM_2P";"";"";
"JOYSTICK";"FLIP_TYPE_0.5_5P";"FPC-05WAY0.5";"FPC-0.5MM-05WAY";"";"";
"JP1";"10-WAY";"10-WAY";"1X10_FEMALE_SMT_RIGHT_ANGLE";"Header 10";"";
"L1";"NRS5030T1R0NMGJ";"NRS5030";"NRS5030";"";"";
"L2";"NR4018T4R7M";"NR4018T4R7M";"NR4018";"";"";
"Q5";"DMN3023L";"MOSFET-NCHANNEL";"SOT23";"";"";
"R1";"100k";"R-EU_R0603";"R0603";"RESISTOR, European symbol";"";
"R2";"1k";"R-EU_R0603";"R0603";"RESISTOR, European symbol";"";
"R3";"1k";"R-EU_R0603";"R0603";"RESISTOR, European symbol";"";
"R5";"10k";"R-EU_R0603";"R0603";"RESISTOR, European symbol";"";
"R6";"47K";"R-EU_R0603";"R0603";"RESISTOR, European symbol";"";
"R7";"13.7R";"R-EU_R0603";"R0603";"RESISTOR, European symbol";"";
"R8";"20K";"R-EU_R0603";"R0603";"RESISTOR, European symbol";"";
"R9";"1k";"R-EU_R0603";"R0603";"RESISTOR, European symbol";"";
"R10";"1M";"R-EU_R0603";"R0603";"RESISTOR, European symbol";"";
"R11";"1M";"R-EU_R0603";"R0603";"RESISTOR, European symbol";"";
"R12";"430k";"R-EU_R0603";"R0603";"RESISTOR, European symbol";"";
"R13";"100k";"R-EU_R0603";"R0603";"RESISTOR, European symbol";"";
"R17";"1k";"R-EU_R0603";"R0603";"RESISTOR, European symbol";"";
"R18";"1k";"R-EU_R0603";"R0603";"RESISTOR, European symbol";"";
"R19";"10k";"R-EU_R0603";"R0603";"RESISTOR, European symbol";"";
"R20";"10k";"R-EU_R0603";"R0603";"RESISTOR, European symbol";"";
"R21";"10k";"R-EU_R0603";"R0603";"RESISTOR, European symbol";"";
"R24";"100k";"R-EU_R0603";"R0603";"RESISTOR, European symbol";"";
"R26";"1k";"R-EU_R0603";"R0603";"RESISTOR, European symbol";"";
"R29";"100k";"R-EU_R0603";"R0603";"RESISTOR, European symbol";"";
"R36";"39k";"R-EU_R0603";"R0603";"RESISTOR, European symbol";"";
"R37";"4k7";"R-EU_R0603";"R0603";"RESISTOR, European symbol";"";
"R38";"4k7";"R-EU_R0603";"R0603";"RESISTOR, European symbol";"";
"R39";"1k";"R-EU_R0603";"R0603";"RESISTOR, European symbol";"";
"R40";"390R";"R-EU_R0603";"R0603";"RESISTOR, European symbol";"";
"RGB1";"LED_RGB_4P6028_REVERSE";"LED_RGB_4P6028_REVERSE";"LED-6028_REVERSE_RGB";"";"";
"RGB2";"LED_RGB_4P6028_REVERSE";"LED_RGB_4P6028_REVERSE";"LED-6028_REVERSE_RGB";"";"";
"SJ1";"";"SOLDERJUMPER";"SOLDERJUMPER_ARROW_NOPASTE";"SMD Solder JUMPER";"";
"STM32H750";"";"STM32H750VB";"LQFP-100";"";"";
"SWRESET";"LY-A03-02";"TACT_SWITCHLOWPROFILE";"TACT_RIGHT_ANGLE_LOW_PROFILE";"";"";
"U$3";"FCI 10118193-0001LF";"USBMICROB";"MICROB-USB";"";"";
"U$17";"FIDUCIAL1MM";"FIDUCIAL1MM";"FIDUCIAL-1MM";"2mm fiducial for pick and place";"";
"U$18";"HOME-MENU";"HOME-MENU";"MENU-HOME";"";"";
"U$19";"ABM8G-12.000MHZ-4Y-T3";"TSX-3225";"TSX-3225";"";"";
"U$22";"FIDUCIAL1MM";"FIDUCIAL1MM";"FIDUCIAL-1MM";"2mm fiducial for pick and place";"";
"U$23";"FIDUCIAL1MM";"FIDUCIAL1MM";"FIDUCIAL-1MM";"2mm fiducial for pick and place";"";
"U1";"SN74AHC1G02";"SN74AHC1G02";"SOT-23-5";"";"";
"U3";"AP3031KTR-G1 - ref 200mV";"AP30XX_OVP";"SOT23-6L";"";"";
"U4";"";"ACCEL_LIS3DHTR";"LGA16_3X3MM";"LIS3DHTR 3-Axis Accelerometer with I2C/SPI Interface";"";
"U5";"PAM8301";"PAM8301";"SOT-23-6";"";"";
"U6";"AP2112";"AP2112";"SOT-23-5";"";"";
"U8";"74VHC4053AFT";"74VHC4053AFT";"TSSOP-16-TI";"";"";
"U11";"BQ24295";"BQ24295";"QFN50P400X400X100-25N";"Stand-Alone Synchronous Switch-Mode";"";
"U22";"MT25QL256ABA1EW7-0SIT";"SPI_QUAD_FLASH";"DFN-8_6X5MM";"";"";
"USER_3V3_1";"TPTP17SQ";"TPTP17SQ";"TP17SQ";"Test pad";"";
"USER_3V3_2";"TPTP17SQ";"TPTP17SQ";"TP17SQ";"Test pad";"";
"USER_GND_1";"TPTP17SQ";"TPTP17SQ";"TP17SQ";"Test pad";"";
"USER_GND_2";"TPTP17SQ";"TPTP17SQ";"TP17SQ";"Test pad";"";
"USER_LEFT1";"TPTP17SQ";"TPTP17SQ";"TP17SQ";"Test pad";"";
"USER_LEFT2";"TPTP17SQ";"TPTP17SQ";"TP17SQ";"Test pad";"";
"USER_RIGHT1";"TPTP17SQ";"TPTP17SQ";"TP17SQ";"Test pad";"";
"USER_RIGHT2";"TPTP17SQ";"TPTP17SQ";"TP17SQ";"Test pad";"";
"X1";"MicroSD";"MICROSD";"MICROSD";"MicroSD/Transflash Card Holder with SPI pinout";"";

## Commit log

2021-05-21 Add BOM
2023-02-23 Add mechanical design files.
2023-02-23 Add PCB.
2023-03-01 Sync CubeMX IOC project file with final hardware
    Final hardware uses a 12MHz crystal on HSE. Dividers are synced to
    match those used in the firmware. I have also checked all GPIO
    functions against the PDF schematic and firmware.
    Note that some very early pre-beta boards use different crystals.
2023-03-01 Delete the duplicate Eagle schematic in root
    It was identical to the one recently added to pcb subdirectory.

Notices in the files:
parts and their libraries:
microbuilder: This work is placed in the public domain, and may be freely used for commercial and non-commercial work with the following conditions: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
pimoroni: Licensing: CC v3.0 Share-Alike You are welcome to use this library for commercial purposes.
